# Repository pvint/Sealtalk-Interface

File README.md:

# Sealtalk-Interface
Seatalk to TTL level RS-232 Interface Module for ESP32 or Raspberry Pi

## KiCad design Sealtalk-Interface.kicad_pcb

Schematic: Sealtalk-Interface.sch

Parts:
J1, J2: Screw_Terminal_01x02; SCREW TERMINAL BLOCK 3.5MM 2POS
J3: Conn_02x05_Odd_Even; PinSocket_2x05_P2.54mm_Vertical
JP1: SolderJumper_3_Bridged12; SolderJumper-3_P1.3mm_Bridged2Bar12_Pad1.0x1.5mm_NumberLabe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
Q1, Q2, Q4: MMBT2222A; SOT-23
Q3: MMBT2907A; SOT-23
R1, R2, R4, R7: 10k; R_0805_2012Metric
R3: R; R_0805_2012Metric
R5: 2k2; R_0805_2012Metric
R6: 1k; R_0805_2012Metric

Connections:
GND: J2.2, J3.9, Q1.2 (E), R3.2, R6.2, R7.2
GPIO: J3.7, JP1.1
unnamed: Q1.1 (B), R1.1
unnamed: Q1.3 (C), Q4.1 (B), R2.2
unnamed: Q2.1 (B), R4.1, R5.2
unnamed: Q2.2 (E), Q3.1 (B), R7.1
unnamed: Q4.2 (E), R3.1
Rx: J1.1, J3.8, R1.2
SeatalkData: J2.1, Q4.3 (C), R4.2
Tx: J1.2, JP1.2, Q3.3 (C), R6.1
VCC: J3.1, Q2.3 (C), Q3.2 (E), R2.1, R5.1
toRx: J3.10, JP1.3

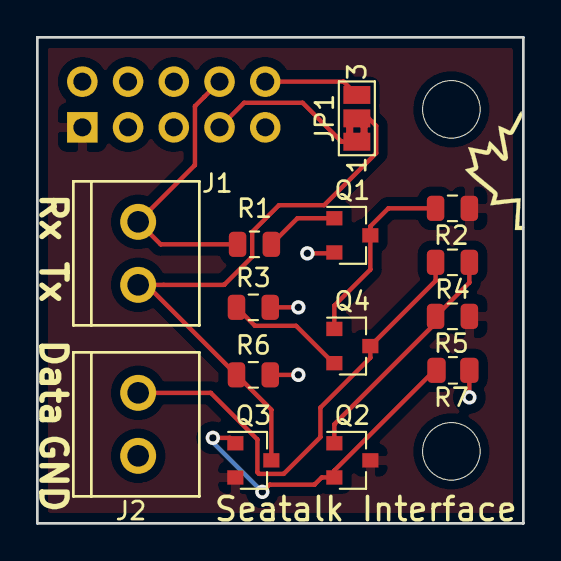
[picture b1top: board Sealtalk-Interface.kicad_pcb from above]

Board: 2 copper layers, 27.0 x 27.0 mm, 15 parts (1 on the bottom side), 12 nets.

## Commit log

2020-08-13 Schematic and inital board layout done - pending audit
2020-08-13 Added jumper to configure Rx, fixed 2x5 header
2020-08-13 Silk edits
2020-11-23 RevB fixes
